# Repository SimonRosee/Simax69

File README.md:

# Simax69 Keyboards

Some attempts on my own to create a custom mechanical keyboard

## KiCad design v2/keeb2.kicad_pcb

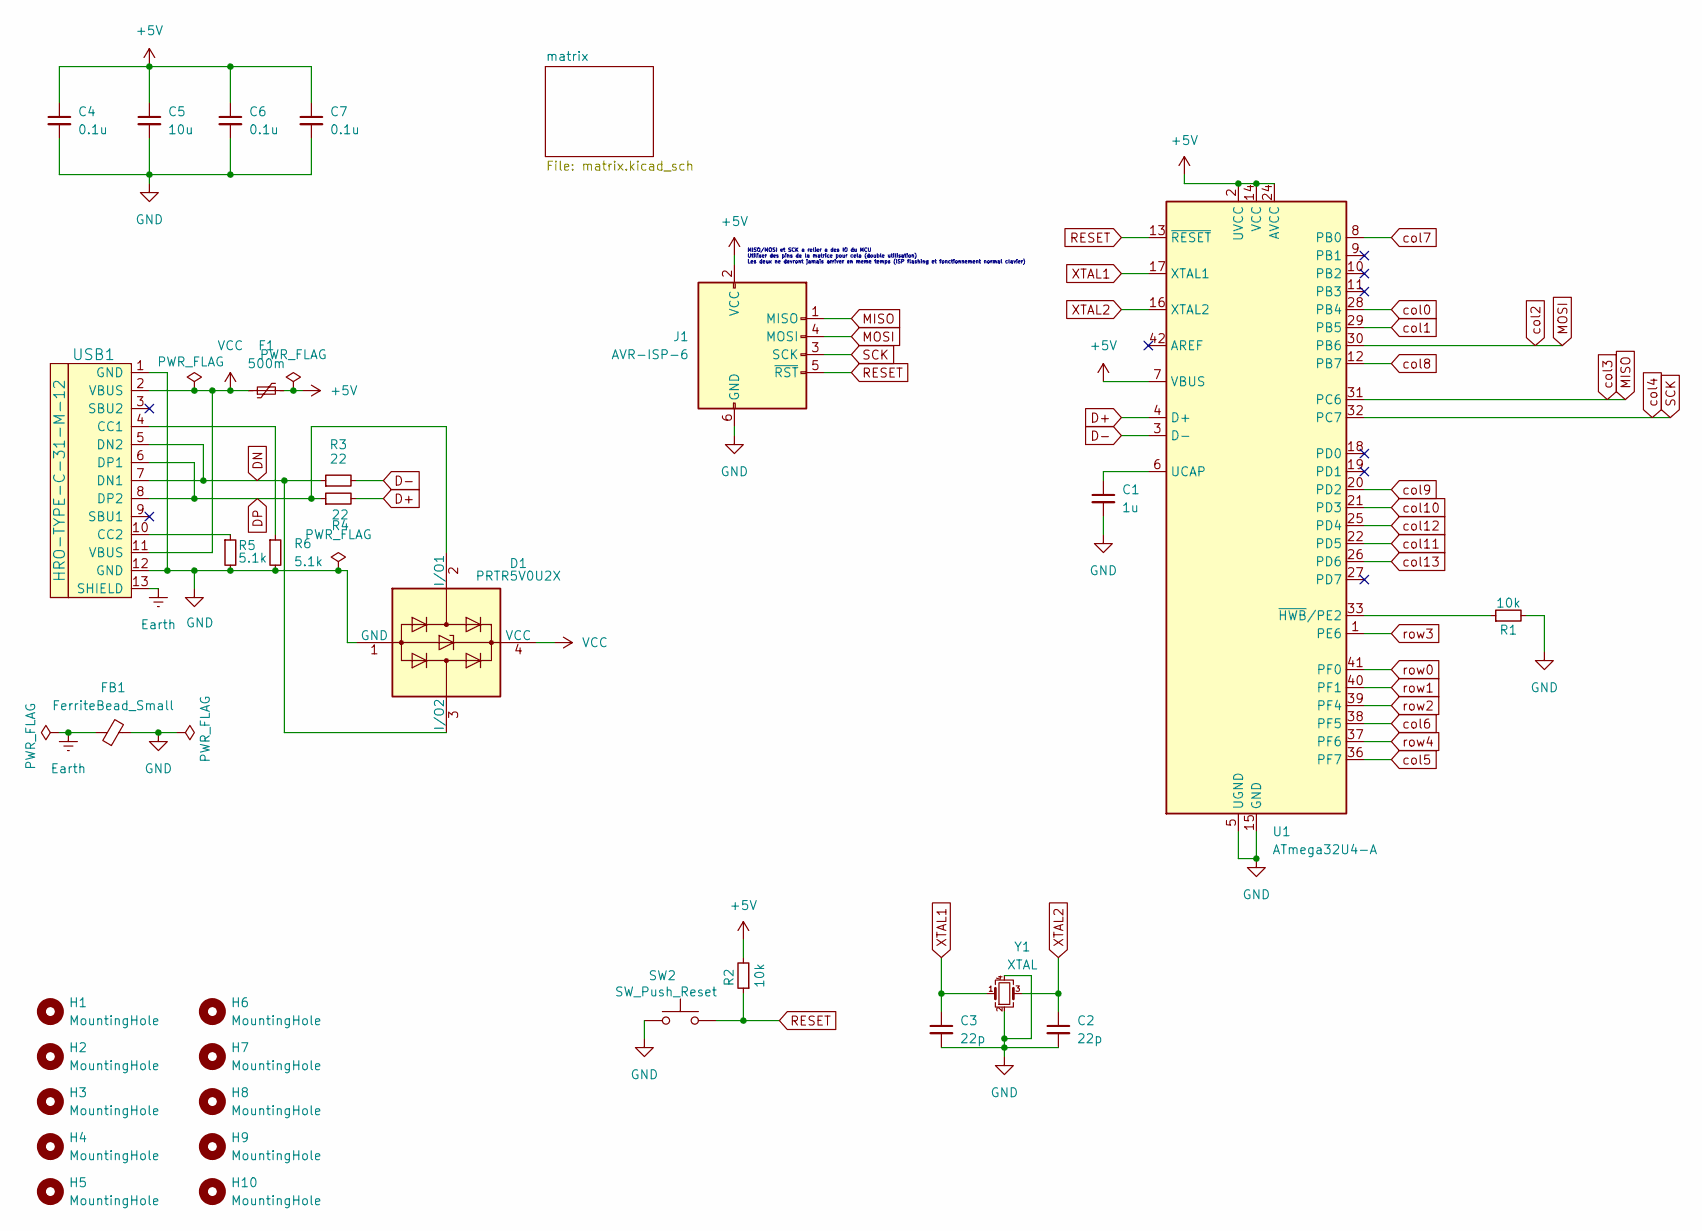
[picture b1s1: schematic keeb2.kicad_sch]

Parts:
C1: 1u; C_0805_2012Metric_Pad1.18x1.45mm_HandSolder
C2, C3: 22p; C_0805_2012Metric_Pad1.18x1.45mm_HandSolder
C4, C6, C7: 0.1u; C_0805_2012Metric_Pad1.18x1.45mm_HandSolder
C5: 10u; C_0805_2012Metric_Pad1.18x1.45mm_HandSolder
D1: PRTR5V0U2X; SOT-143_Handsoldering
F1: 500m; Fuse_1206_3216Metric_Pad1.42x1.75mm_HandSolder
FB1: FerriteBead_Small; L_0805_2012Metric_Pad1.15x1.40mm_HandSolder
H1, H2, H3, H4, H5, H6, H7, H8, H9, H10: MountingHole; MountingHole_2.1mm
J1: AVR-ISP-6; Reset_Pretty-Mask
R1, R2: 10k; R_0805_2012Metric_Pad1.20x1.40mm_HandSolder
R3, R4: 22; R_0805_2012Metric_Pad1.20x1.40mm_HandSolder
R5, R6: 5.1k; R_0805_2012Metric_Pad1.20x1.40mm_HandSolder
SW2: SW_Push_Reset; SW_SPST_SKQG_WithStem
U1: ATmega32U4-A; TQFP-44_10x10mm_P0.8mm
USB1: HRO-TYPE-C-31-M-12; HRO-TYPE-C-31-M-12-HandSoldering
Y1: XTAL; Crystal_SMD_3225-4Pin_3.2x2.5mm_HandSoldering

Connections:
+5V: C4.1, C5.1, C6.1, C7.1, F1.2, J1.2 (VCC), R2.2, U1.2 (UVCC), U1.7 (VBUS), U1.14 (VCC), U1.24 (AVCC), U1.34 (VCC), U1.44 (AVCC)
D+: R4.2, U1.4 (D+)
D-: R3.2, U1.3 (D-)
DN: D1.3 (I/O2), R3.1, USB1.5 (DN2), USB1.7 (DN1)
DP: D1.2 (I/O1), R4.1, USB1.6 (DP1), USB1.8 (DP2)
Earth: FB1.1, USB1.13 (SHIELD)
GND: C1.2, C2.2, C3.2, C4.2, C5.2, C6.2, C7.2, D1.1 (GND), FB1.2, J1.6 (GND), R1.2, R5.2, R6.2, SW2.1, U1.5 (UGND), U1.15 (GND), U1.23 (GND), U1.35 (GND), U1.43 (GND), USB1.1 (GND), USB1.12 (GND), Y1.2, Y1.4
MISO: J1.1 (MISO), U1.31 (PC6); also elsewhere on the board
MOSI: J1.4 (MOSI), U1.30 (PB6); also elsewhere on the board
unnamed: C1.1, U1.6 (UCAP)
unnamed: R1.1, U1.33 (~HWB/PE2)
unnamed: R6.1, USB1.4 (CC1)
unnamed: R5.1, USB1.10 (CC2)
RESET: J1.5 (~RST), R2.1, SW2.2, U1.13 (~RESET)
SCK: J1.3 (SCK), U1.32 (PC7); also elsewhere on the board
VCC: D1.4 (VCC), F1.1, USB1.2 (VBUS), USB1.11 (VBUS)
XTAL1: C3.1, U1.17 (XTAL1), Y1.1
XTAL2: C2.1, U1.16 (XTAL2), Y1.3
col0: U1.28 (PB4); also elsewhere on the board
col1: U1.29 (PB5); also elsewhere on the board
col5: U1.36 (PF7); also elsewhere on the board
col6: U1.38 (PF5); also elsewhere on the board
col7: U1.8 (PB0); also elsewhere on the board
col8: U1.12 (PB7); also elsewhere on the board
col9: U1.20 (PD2); also elsewhere on the board
col10: U1.21 (PD3); also elsewhere on the board
col11: U1.22 (PD5); also elsewhere on the board
col12: U1.25 (PD4); also elsewhere on the board
col13: U1.26 (PD6); also elsewhere on the board
row0: U1.41 (PF0); also elsewhere on the board
row1: U1.40 (PF1); also elsewhere on the board
row2: U1.39 (PF4); also elsewhere on the board
row3: U1.1 (PE6); also elsewhere on the board
row4: U1.37 (PF6); also elsewhere on the board

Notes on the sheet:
MISO/MOSI et SCK a relier a des IO du MCU Utiliser des pins de la matrice pour cela (double utilisation) Les deux ne devront jamais arriver en meme temps (ISP flashing et fonctionnement normal clavier)

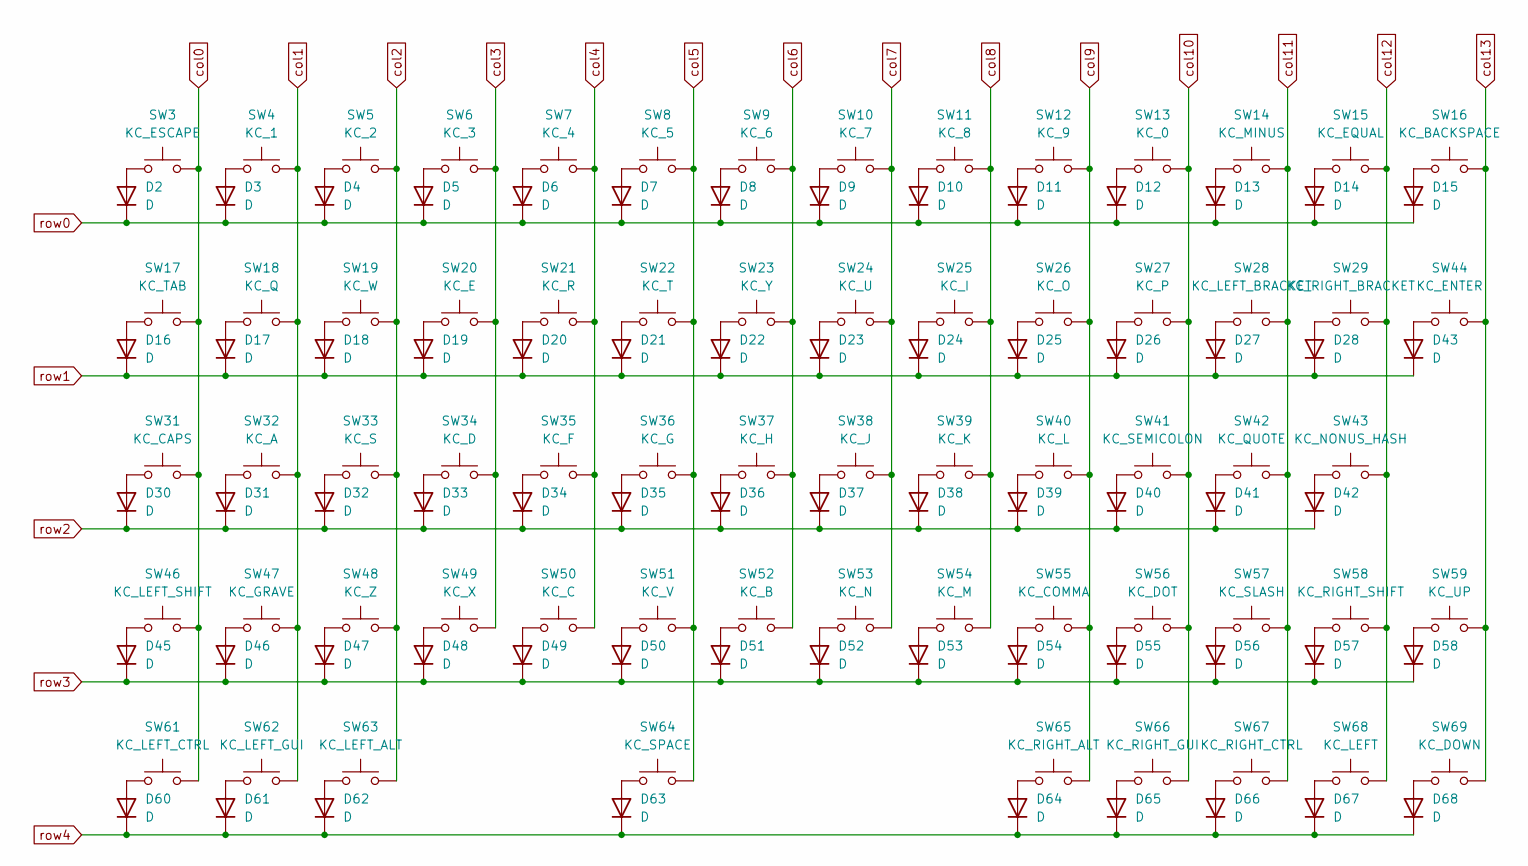
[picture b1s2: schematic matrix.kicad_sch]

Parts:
D2, D3, D4, D5, D6, D7, D8, D9, D10, D11, D12, D13, D14, D15, D16, D17, D18, D19, D20, D21, D22, D23, D24, D25, D26, D27, D28, D30, D31, D32, D33, D34, D35, D36, D37, D38, D39, D40, D41, D42, D43, D45, D46, D47, D48, D49, D50, D51, D52, D53, D54, D55, D56, D57, D58, D60, D61, D62, D63, D64, D65, D66, D67, D68: D; D_SOD-123
SW3: KC_ESCAPE; SW_Cherry_MX_1.00u_PCB
SW4: KC_1; SW_Cherry_MX_1.00u_PCB
SW5: KC_2; SW_Cherry_MX_1.00u_PCB
SW6: KC_3; SW_Cherry_MX_1.00u_PCB
SW7: KC_4; SW_Cherry_MX_1.00u_PCB
SW8: KC_5; SW_Cherry_MX_1.00u_PCB
SW9: KC_6; SW_Cherry_MX_1.00u_PCB
SW10: KC_7; SW_Cherry_MX_1.00u_PCB
SW11: KC_8; SW_Cherry_MX_1.00u_PCB
SW12: KC_9; SW_Cherry_MX_1.00u_PCB
SW13: KC_0; SW_Cherry_MX_1.00u_PCB
SW14: KC_MINUS; SW_Cherry_MX_1.00u_PCB
SW15: KC_EQUAL; SW_Cherry_MX_1.00u_PCB
SW16: KC_BACKSPACE; SW_Cherry_MX_2.00u_PCB
SW17: KC_TAB; SW_Cherry_MX_1.50u_PCB
SW18: KC_Q; SW_Cherry_MX_1.00u_PCB
SW19: KC_W; SW_Cherry_MX_1.00u_PCB
SW20: KC_E; SW_Cherry_MX_1.00u_PCB
SW21: KC_R; SW_Cherry_MX_1.00u_PCB
SW22: KC_T; SW_Cherry_MX_1.00u_PCB
SW23: KC_Y; SW_Cherry_MX_1.00u_PCB
SW24: KC_U; SW_Cherry_MX_1.00u_PCB
SW25: KC_I; SW_Cherry_MX_1.00u_PCB
SW26: KC_O; SW_Cherry_MX_1.00u_PCB
SW27: KC_P; SW_Cherry_MX_1.00u_PCB
SW28: KC_LEFT_BRACKET; SW_Cherry_MX_1.00u_PCB
SW29: KC_RIGHT_BRACKET; SW_Cherry_MX_1.00u_PCB
SW31: KC_CAPS; SW_Cherry_MX_1.75u_PCB
SW32: KC_A; SW_Cherry_MX_1.00u_PCB
SW33: KC_S; SW_Cherry_MX_1.00u_PCB
SW34: KC_D; SW_Cherry_MX_1.00u_PCB
SW35: KC_F; SW_Cherry_MX_1.00u_PCB
SW36: KC_G; SW_Cherry_MX_1.00u_PCB
SW37: KC_H; SW_Cherry_MX_1.00u_PCB
SW38: KC_J; SW_Cherry_MX_1.00u_PCB
SW39: KC_K; SW_Cherry_MX_1.00u_PCB
SW40: KC_L; SW_Cherry_MX_1.00u_PCB
SW41: KC_SEMICOLON; SW_Cherry_MX_1.00u_PCB
SW42: KC_QUOTE; SW_Cherry_MX_1.00u_PCB
SW43: KC_NONUS_HASH; SW_Cherry_MX_1.00u_PCB
SW44: KC_ENTER; SW_Cherry_MX_ISOEnter_PCB
SW46: KC_LEFT_SHIFT; SW_Cherry_MX_1.25u_PCB
SW47: KC_GRAVE; SW_Cherry_MX_1.00u_PCB
SW48: KC_Z; SW_Cherry_MX_1.00u_PCB
SW49: KC_X; SW_Cherry_MX_1.00u_PCB
SW50: KC_C; SW_Cherry_MX_1.00u_PCB
SW51: KC_V; SW_Cherry_MX_1.00u_PCB
SW52: KC_B; SW_Cherry_MX_1.00u_PCB
SW53: KC_N; SW_Cherry_MX_1.00u_PCB
SW54: KC_M; SW_Cherry_MX_1.00u_PCB
SW55: KC_COMMA; SW_Cherry_MX_1.00u_PCB
SW56: KC_DOT; SW_Cherry_MX_1.00u_PCB
SW57: KC_SLASH; SW_Cherry_MX_1.00u_PCB
SW58: KC_RIGHT_SHIFT; SW_Cherry_MX_1.75u_PCB
SW59: KC_UP; SW_Cherry_MX_1.00u_PCB
SW61: KC_LEFT_CTRL; SW_Cherry_MX_1.25u_PCB
SW62: KC_LEFT_GUI; SW_Cherry_MX_1.25u_PCB
SW63: KC_LEFT_ALT; SW_Cherry_MX_1.25u_PCB
SW64: KC_SPACE; SW_Cherry_MX_6.25u_PCB
SW65: KC_RIGHT_ALT; SW_Cherry_MX_1.00u_PCB
SW66: KC_RIGHT_GUI; SW_Cherry_MX_1.00u_PCB
SW67: KC_RIGHT_CTRL; SW_Cherry_MX_1.00u_PCB
SW68: KC_LEFT; SW_Cherry_MX_1.00u_PCB
SW69: KC_DOWN; SW_Cherry_MX_1.00u_PCB

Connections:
MISO: SW6.2, SW20.2, SW34.2, SW49.2; also elsewhere on the board
MOSI: SW5.2, SW19.2, SW33.2, SW48.2, SW63.2; also elsewhere on the board
unnamed: D2.2 (A), SW3.1
unnamed: D3.2 (A), SW4.1
unnamed: D4.2 (A), SW5.1
unnamed: D5.2 (A), SW6.1
unnamed: D6.2 (A), SW7.1
unnamed: D7.2 (A), SW8.1
unnamed: D8.2 (A), SW9.1
unnamed: D9.2 (A), SW10.1
unnamed: D10.2 (A), SW11.1
unnamed: D11.2 (A), SW12.1
unnamed: D12.2 (A), SW13.1
unnamed: D13.2 (A), SW14.1
unnamed: D14.2 (A), SW15.1
unnamed: D15.2 (A), SW16.1
unnamed: D16.2 (A), SW17.1
unnamed: D17.2 (A), SW18.1
unnamed: D18.2 (A), SW19.1
unnamed: D19.2 (A), SW20.1
unnamed: D20.2 (A), SW21.1
unnamed: D21.2 (A), SW22.1
unnamed: D22.2 (A), SW23.1
unnamed: D23.2 (A), SW24.1
unnamed: D24.2 (A), SW25.1
unnamed: D25.2 (A), SW26.1
unnamed: D26.2 (A), SW27.1
unnamed: D27.2 (A), SW28.1
unnamed: D28.2 (A), SW29.1
unnamed: D30.2 (A), SW31.1
unnamed: D31.2 (A), SW32.1
unnamed: D32.2 (A), SW33.1
unnamed: D33.2 (A), SW34.1
unnamed: D34.2 (A), SW35.1
unnamed: D35.2 (A), SW36.1
unnamed: D36.2 (A), SW37.1
unnamed: D37.2 (A), SW38.1
unnamed: D38.2 (A), SW39.1
unnamed: D39.2 (A), SW40.1
unnamed: D40.2 (A), SW41.1
unnamed: D41.2 (A), SW42.1
unnamed: D42.2 (A), SW43.1
unnamed: D43.2 (A), SW44.1
unnamed: D45.2 (A), SW46.1
unnamed: D46.2 (A), SW47.1
unnamed: D47.2 (A), SW48.1
unnamed: D48.2 (A), SW49.1
unnamed: D49.2 (A), SW50.1
unnamed: D50.2 (A), SW51.1
unnamed: D51.2 (A), SW52.1
unnamed: D52.2 (A), SW53.1
unnamed: D53.2 (A), SW54.1
unnamed: D54.2 (A), SW55.1
unnamed: D55.2 (A), SW56.1
unnamed: D56.2 (A), SW57.1
unnamed: D57.2 (A), SW58.1
unnamed: D58.2 (A), SW59.1
unnamed: D60.2 (A), SW61.1
unnamed: D61.2 (A), SW62.1
unnamed: D62.2 (A), SW63.1
unnamed: D63.2 (A), SW64.1
unnamed: D64.2 (A), SW65.1
unnamed: D65.2 (A), SW66.1
unnamed: D66.2 (A), SW67.1
unnamed: D67.2 (A), SW68.1
unnamed: D68.2 (A), SW69.1
SCK: SW7.2, SW21.2, SW35.2, SW50.2; also elsewhere on the board
col0: SW3.2, SW17.2, SW31.2, SW46.2, SW61.2; also elsewhere on the board
col1: SW4.2, SW18.2, SW32.2, SW47.2, SW62.2; also elsewhere on the board
col5: SW8.2, SW22.2, SW36.2, SW51.2, SW64.2; also elsewhere on the board
col6: SW9.2, SW23.2, SW37.2, SW52.2; also elsewhere on the board
col7: SW10.2, SW24.2, SW38.2, SW53.2; also elsewhere on the board
col8: SW11.2, SW25.2, SW39.2, SW54.2; also elsewhere on the board
col9: SW12.2, SW26.2, SW40.2, SW55.2, SW65.2; also elsewhere on the board
col10: SW13.2, SW27.2, SW41.2, SW56.2, SW66.2; also elsewhere on the board
col11: SW14.2, SW28.2, SW42.2, SW57.2, SW67.2; also elsewhere on the board
col12: SW15.2, SW29.2, SW43.2, SW58.2, SW68.2; also elsewhere on the board
col13: SW16.2, SW44.2, SW59.2, SW69.2; also elsewhere on the board
row0: D2.1 (K), D3.1 (K), D4.1 (K), D5.1 (K), D6.1 (K), D7.1 (K), D8.1 (K), D9.1 (K), D10.1 (K), D11.1 (K), D12.1 (K), D13.1 (K), D14.1 (K), D15.1 (K); also elsewhere on the board
row1: D16.1 (K), D17.1 (K), D18.1 (K), D19.1 (K), D20.1 (K), D21.1 (K), D22.1 (K), D23.1 (K), D24.1 (K), D25.1 (K), D26.1 (K), D27.1 (K), D28.1 (K), D43.1 (K); also elsewhere on the board
row2: D30.1 (K), D31.1 (K), D32.1 (K), D33.1 (K), D34.1 (K), D35.1 (K), D36.1 (K), D37.1 (K), D38.1 (K), D39.1 (K), D40.1 (K), D41.1 (K), D42.1 (K); also elsewhere on the board
row3: D45.1 (K), D46.1 (K), D47.1 (K), D48.1 (K), D49.1 (K), D50.1 (K), D51.1 (K), D52.1 (K), D53.1 (K), D54.1 (K), D55.1 (K), D56.1 (K), D57.1 (K), D58.1 (K); also elsewhere on the board
row4: D60.1 (K), D61.1 (K), D62.1 (K), D63.1 (K), D64.1 (K), D65.1 (K), D66.1 (K), D67.1 (K), D68.1 (K); also elsewhere on the board

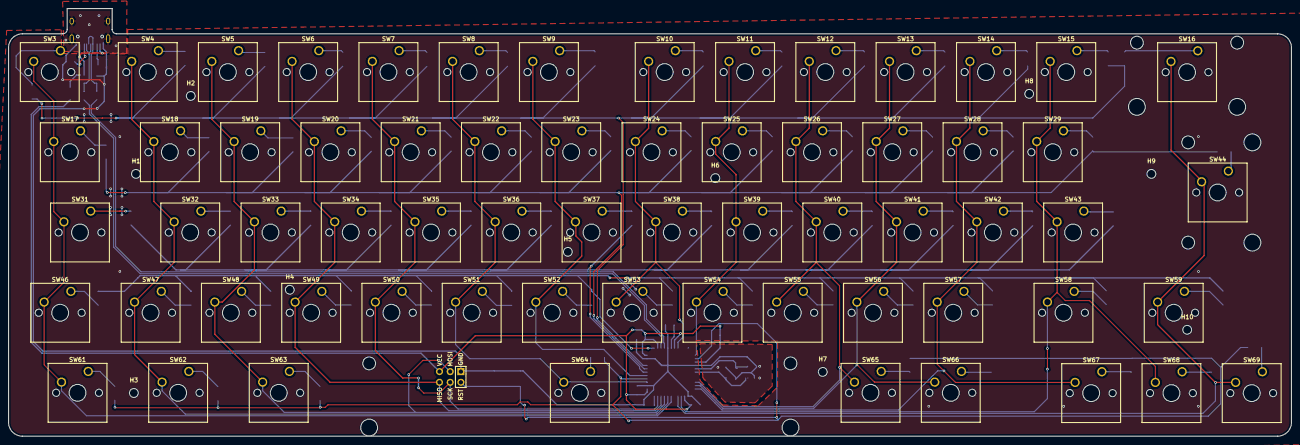
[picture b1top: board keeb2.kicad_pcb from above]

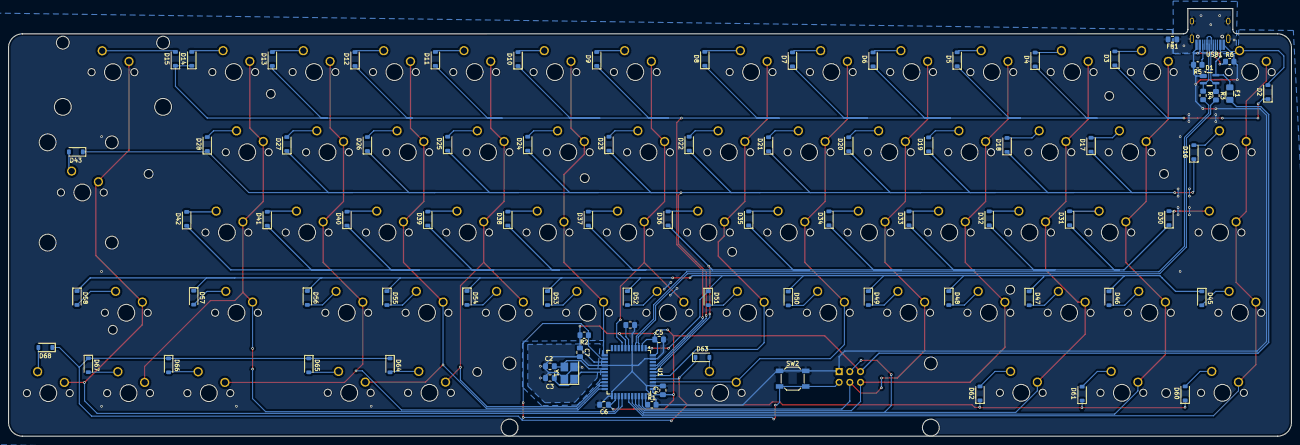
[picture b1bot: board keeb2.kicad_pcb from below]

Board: 2 copper layers, 304.5 x 101.5 mm, 159 parts (84 on the bottom side), 98 nets.

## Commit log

2024-10-08 Rename fp-info-cache to v2/fp-info-cache
2024-10-08 Rename keeb2.kicad_prl to v2/keeb2.kicad_prl
2024-10-08 Rename keeb2.kicad_pro to v2/keeb2.kicad_pro
2024-10-08 Rename keyboard-layout(2).json to v2/keyboard-layout(2).json
2024-10-08 Add version 1 of Simax69
    Add the blender file, the 3D stl files and a few early representations of the project
2024-10-09 Added Keebio-Parts and Type-C submodule
2024-10-09 Changed switch value for better understanding in PCB view
2024-10-11 Changed switch footprint to MX footprint
    Realised I didn't want Alp switch so changed to more classic MX switch.
    Need a full redone of the routing :'(
2024-10-11 Linked part of the design; need to move reset button & ISP
2024-10-14 Moved ISP and reset button. Finished routing
    Moved the ISP IO to make it easier to route them to the MCU
2024-10-14 Added dimension of the pcb
2024-10-25 First try at manufacturing files
2025-06-06 Change outline to fit new case
    Add mounting holes at correct location
    case height : 96 mm
    pcb height : 95.5mm
    case length : 305 mm
    pcb length : 304.5 mm
2025-06-06 squeeze keyboard in case
    removed colomn 14 (4 keys), TTRS connection, and rotary encoder
2025-07-19 Finished routing
2025-07-19 Small adjustement
2025-07-20 Added gnd layers and ferrite bead on USB
2025-07-20 Manufacturing files
